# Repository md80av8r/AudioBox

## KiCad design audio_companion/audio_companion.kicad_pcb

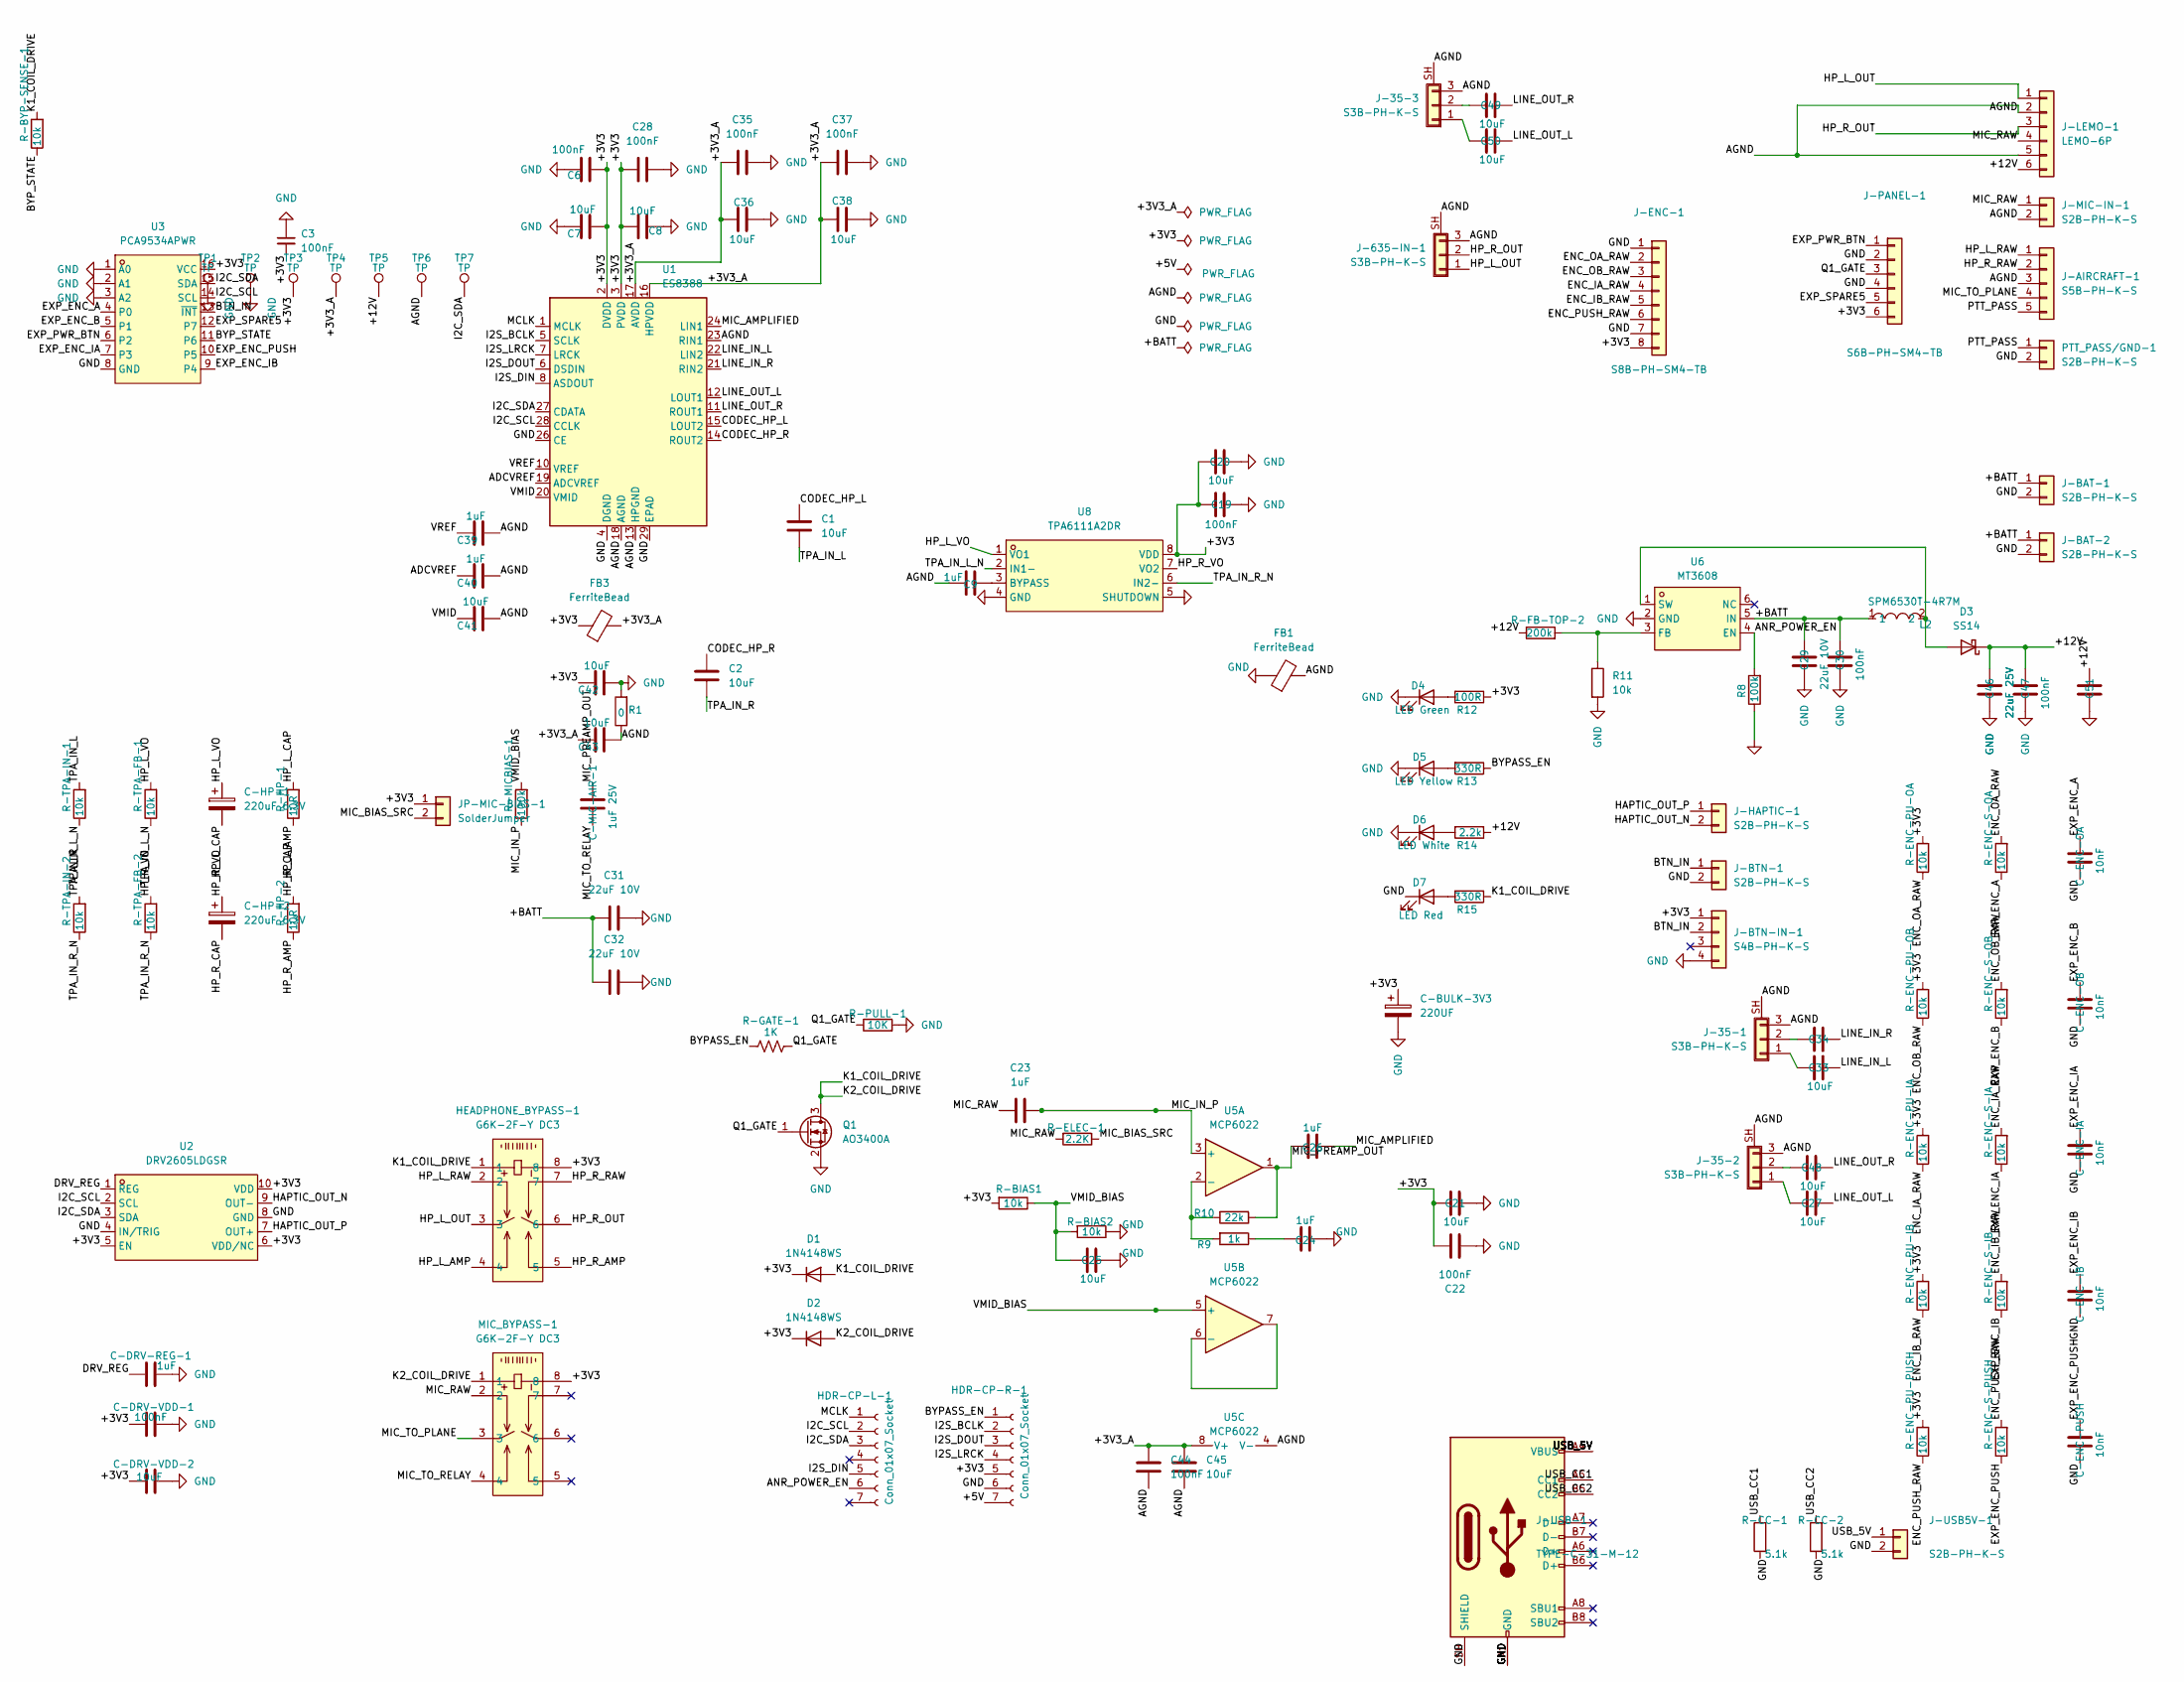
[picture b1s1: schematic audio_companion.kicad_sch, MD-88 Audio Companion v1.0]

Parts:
C1, C2: 10uF; C_0805_2012Metric
C3, C6, C19, C22, C28, C30, C35, C37, C44, C47: 100nF; C_0402_1005Metric
C7, C8, C20, C21, C25, C27, C33, C34, C36, C38, C41, C42, C43, C45, C48, C49, C50: 10uF; C_0402_1005Metric
C9, C23, C24, C26, C39, C40: 1uF; C_0402_1005Metric
C29, C31, C32: 22uF 10V; C_0805_2012Metric
C46, C51: 22uF 25V; C_0805_2012Metric
C-BULK-3V3: 220UF; CP_EIA-6032-28_Kemet-C
C-DRV-REG-1: 1uF; C_0402_1005Metric
C-DRV-VDD-1: 100nF; C_0402_1005Metric
C-DRV-VDD-2: 10uF; C_0402_1005Metric
C-ENC-IA: 10nF; C_0402_1005Metric
C-ENC-IB: 10nF; C_0402_1005Metric
C-ENC-OA: 10nF; C_0402_1005Metric
C-ENC-OB: 10nF; C_0402_1005Metric
C-ENC-PUSH: 10nF; C_0402_1005Metric
C-HP-1, C-HP-2: 220uF 6.3V; CP_EIA-6032-28_Kemet-C
C-MIC-AIR-1: 1uF 25V; C_0402_1005Metric
D1, D2: 1N4148WS; D_SOD-323
D3: SS14; D_SMA
D4: LED Green; LED_0603_1608Metric
D5: LED Yellow; LED_0603_1608Metric
D6: LED White; LED_0603_1608Metric
D7: LED Red; LED_0603_1608Metric
FB1, FB3: FerriteBead; L_0603_1608Metric
HDR-CP-L-1: Conn_01x07_Socket; PinHeader_1x07_P2.54mm_Vertical
HDR-CP-R-1: Conn_01x07_Socket; PinHeader_1x07_P2.54mm_Vertical
HEADPHONE_BYPASS-1: G6K-2F-Y DC3; Relay_DPDT_Omron_G6K-2F-Y; MPN G6K-2F-Y DC3; LCSC Part C93168
J-35-1, J-35-2, J-35-3, J-635-IN-1: S3B-PH-K-S; JST_PH_S3B-PH-K_1x03_P2.00mm_Horizontal
J-AIRCRAFT-1: S5B-PH-K-S; JST_PH_S5B-PH-K_1x05_P2.00mm_Horizontal
J-BAT-1, J-BAT-2: S2B-PH-K-S; JST_PH_S2B-PH-K_1x02_P2.00mm_Horizontal
J-BTN-1: S2B-PH-K-S; JST_PH_S2B-PH-K_1x02_P2.00mm_Horizontal
J-BTN-IN-1: S4B-PH-K-S; JST_PH_S4B-PH-K_1x04_P2.00mm_Horizontal
J-ENC-1: S8B-PH-SM4-TB; JST_PH_S8B-PH-SM4-TB_1x08-1MP_P2.00mm_Horizontal; MPN S8B-PH-SM4-TB(LF)(SN)
J-HAPTIC-1: S2B-PH-K-S; JST_PH_S2B-PH-K_1x02_P2.00mm_Horizontal
J-LEMO-1: LEMO-6P; PinHeader_1x06_P2.54mm_Vertical
J-MIC-IN-1: S2B-PH-K-S; JST_PH_S2B-PH-K_1x02_P2.00mm_Horizontal
J-PANEL-1: S6B-PH-SM4-TB; JST_PH_S6B-PH-SM4-TB_1x06-1MP_P2.00mm_Horizontal; MPN S6B-PH-SM4-TB(LF)(SN)
J-USB5V-1: S2B-PH-K-S; JST_PH_S2B-PH-K_1x02_P2.00mm_Horizontal; MPN S2B-PH-K-S
J-USB-1: TYPE-C-31-M-12; USB_C_Receptacle_HRO_TYPE-C-31-M-12; MPN TYPE-C-31-M-12; LCSC C165948
JP-MIC-BIAS-1: SolderJumper; SolderJumper-2_P1.3mm_Open_Pad1.0x1.5mm
L2: SPM6530T-4R7M; IND-SMD_L7.1-W6.5; MPN SPM6530T-4R7M; LCSC Part C76857
MIC_BYPASS-1: G6K-2F-Y DC3; Relay_DPDT_Omron_G6K-2F-Y; MPN G6K-2F-Y DC3; LCSC Part C93168
PTT_PASS/GND-1: S2B-PH-K-S; JST_PH_S2B-PH-K_1x02_P2.00mm_Horizontal
Q1: AO3400A; SOT-23
R1: 0; R_0402_1005Metric
R8: 100k; R_0402_1005Metric
R9: 1k; R_0402_1005Metric
R10: 22k; R_0402_1005Metric
R11: 10k; R_0402_1005Metric
R12: 100R; R_0402_1005Metric
R13, R15: 330R; R_0402_1005Metric
R14: 2.2k; R_0402_1005Metric
R-BIAS1, R-BIAS2: 10k; R_0402_1005Metric
R-BYP-SENSE-1: 10k; R_0402_1005Metric
R-CC-1, R-CC-2: 5.1k; R_0402_1005Metric; LCSC C25905
R-ELEC-1: 2.2K; R_0402_1005Metric
R-ENC-PU-IA: 10k; R_0402_1005Metric
R-ENC-PU-IB: 10k; R_0402_1005Metric
R-ENC-PU-OA: 10k; R_0402_1005Metric
R-ENC-PU-OB: 10k; R_0402_1005Metric
R-ENC-PU-PUSH: 10k; R_0402_1005Metric
R-ENC-S-IA: 10k; R_0402_1005Metric
R-ENC-S-IB: 10k; R_0402_1005Metric
R-ENC-S-OA: 10k; R_0402_1005Metric
R-ENC-S-OB: 10k; R_0402_1005Metric
R-ENC-S-PUSH: 10k; R_0402_1005Metric
R-FB-TOP-2: 200k; R_0402_1005Metric
R-GATE-1: 1K; R_0402_1005Metric
R-HP-1, R-HP-2: 10R; R_0402_1005Metric
R-MICBIAS-1: 100k; R_0402_1005Metric
R-PULL-1: 10K; R_0402_1005Metric
R-TPA-FB-1, R-TPA-FB-2: 10k; R_0402_1005Metric
R-TPA-IN-1, R-TPA-IN-2: 10k; R_0402_1005Metric
TP1, TP2, TP3, TP4, TP5, TP6, TP7: TP; TestPoint_Pad_D1.5mm
U1: ES8388; QFN-28-1EP_4x4mm_P0.45mm_EP2.6x2.6mm
U2: DRV2605LDGSR; VSSOP-10_L3.0-W3.0-P0.50-LS4.9-BL; MPN DRV2605LDGSR; LCSC Part C527464
U3: PCA9534APWR; TSSOP-16_L5.0-W4.4-P0.65-LS6.4-BL; MPN PCA9534APWR; LCSC Part C2871127
U5: MCP6022; SOIC-8_3.9x4.9mm_P1.27mm
U6: MT3608; SOT-23-6_L2.9-W1.6-P0.95-LS2.8-BL; MPN MT3608; LCSC Part C84817
U8: TPA6111A2DR; SOIC-8_L5.0-W4.0-P1.27-LS6.0-BL; MPN TPA6111A2DR; LCSC Part C497472

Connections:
/+3V3: C3.2, C6.1, C7.1, C8.1, C19.2, C20.1, C21.1, C22.2, C28.1, C42.2, C-BULK-3V3.1, C-DRV-VDD-1.1, C-DRV-VDD-2.1, D1.1 (K), D2.1 (K), FB3.1, HDR-CP-R-1.5, HEADPHONE_BYPASS-1.8, J-BTN-IN-1.1, J-ENC-1.8, J-PANEL-1.6, JP-MIC-BIAS-1.1, MIC_BYPASS-1.8, R12.1, R-BIAS1.2, R-ENC-PU-IA.2, R-ENC-PU-IB.2, R-ENC-PU-OA.2, R-ENC-PU-OB.2, R-ENC-PU-PUSH.2, TP3.1, U1.2 (DVDD), U1.3 (PVDD), U2.5 (EN), U2.6 (VDD/NC), U2.10 (VDD), U3.16 (VCC), U8.8 (VDD)
/+3V3_A: C35.1, C36.1, C37.1, C38.1, C43.2, C44.1, C45.1, FB3.2, TP4.1, U1.16 (HPVDD), U1.17 (AVDD), U5.8 (V+)
/+5V: HDR-CP-R-1.7
/+12V: C46.1, C47.1, C51.1, D3.1 (K), J-LEMO-1.6, R14.1, R-FB-TOP-2.1, TP5.1
/+BATT: C29.1, C30.1, C31.2, C32.2, J-BAT-1.1, J-BAT-2.1, L2.1, U6.5 (IN)
/ADCVREF: C40.2, U1.19 (ADCVREF)
/AGND: C9.1, C39.1, C40.1, C41.1, C43.1, C44.2, C45.2, FB1.2, J-35-1.3, J-35-1.SH (Shield), J-35-2.3, J-35-2.SH (Shield), J-35-3.3, J-35-3.SH (Shield), J-635-IN-1.3, J-635-IN-1.SH (Shield), J-AIRCRAFT-1.3, J-LEMO-1.2, J-LEMO-1.5, J-MIC-IN-1.2, R1.1, TP6.1, U1.13 (HPGND), U1.18 (AGND), U1.23 (RIN1), U5.4 (V-)
/ANR_POWER_EN: HDR-CP-L-1.6, R8.2, U6.4 (EN)
/BTN_IN: J-BTN-1.1, J-BTN-IN-1.2, U3.13 (~INT)
/BYPASS_EN: HDR-CP-R-1.1, R13.1, R-GATE-1.1
/BYP_STATE: R-BYP-SENSE-1.1, U3.11 (P6)
/CODEC_HP_L: C1.2, U1.15 (LOUT2)
/CODEC_HP_R: C2.2, U1.14 (ROUT2)
/DRV_REG: C-DRV-REG-1.1, U2.1 (REG)
/ENC_IA_RAW: J-ENC-1.4, R-ENC-PU-IA.1, R-ENC-S-IA.2
/ENC_IB_RAW: J-ENC-1.5, R-ENC-PU-IB.1, R-ENC-S-IB.2
/ENC_OA_RAW: J-ENC-1.2, R-ENC-PU-OA.1, R-ENC-S-OA.2
/ENC_OB_RAW: J-ENC-1.3, R-ENC-PU-OB.1, R-ENC-S-OB.2
/ENC_PUSH_RAW: J-ENC-1.6, R-ENC-PU-PUSH.1, R-ENC-S-PUSH.2
/EXP_ENC_A: C-ENC-OA.1, R-ENC-S-OA.1, U3.4 (P0)
/EXP_ENC_B: C-ENC-OB.1, R-ENC-S-OB.1, U3.5 (P1)
/EXP_ENC_IA: C-ENC-IA.1, R-ENC-S-IA.1, U3.7 (P3)
/EXP_ENC_IB: C-ENC-IB.1, R-ENC-S-IB.1, U3.9 (P4)
/EXP_ENC_PUSH: C-ENC-PUSH.1, R-ENC-S-PUSH.1, U3.10 (P5)
/EXP_PWR_BTN: J-PANEL-1.1, U3.6 (P2)
/EXP_SPARE5: J-PANEL-1.5, U3.12 (P7)
/HAPTIC_OUT_N: J-HAPTIC-1.2, U2.9 (OUT-)
/HAPTIC_OUT_P: J-HAPTIC-1.1, U2.7 (OUT+)
/HP_L_AMP: HEADPHONE_BYPASS-1.4, R-HP-1.1
/HP_L_CAP: C-HP-1.2, R-HP-1.2
/HP_L_OUT: HEADPHONE_BYPASS-1.3, J-635-IN-1.1, J-LEMO-1.1
/HP_L_RAW: HEADPHONE_BYPASS-1.2, J-AIRCRAFT-1.1
/HP_L_VO: C-HP-1.1, R-TPA-FB-1.2, U8.1 (VO1)
/HP_R_AMP: HEADPHONE_BYPASS-1.5, R-HP-2.1
/HP_R_CAP: C-HP-2.2, R-HP-2.2
/HP_R_OUT: HEADPHONE_BYPASS-1.6, J-635-IN-1.2, J-LEMO-1.3
/HP_R_RAW: HEADPHONE_BYPASS-1.7, J-AIRCRAFT-1.2
/HP_R_VO: C-HP-2.1, R-TPA-FB-2.2, U8.7 (VO2)
/I2C_SCL: HDR-CP-L-1.2, U1.28 (CCLK), U2.2 (SCL), U3.14 (SCL)
/I2C_SDA: HDR-CP-L-1.3, TP7.1, U1.27 (CDATA), U2.3 (SDA), U3.15 (SDA)
/I2S_BCLK: HDR-CP-R-1.2, U1.5 (SCLK)
/I2S_DIN: HDR-CP-L-1.5, U1.8 (ASDOUT)
/I2S_DOUT: HDR-CP-R-1.3, U1.6 (DSDIN)
/I2S_LRCK: HDR-CP-R-1.4, U1.7 (LRCK)
/K1_COIL_DRIVE: D1.2 (A), D2.2 (A), HEADPHONE_BYPASS-1.1, MIC_BYPASS-1.1, Q1.3 (D), R15.1, R-BYP-SENSE-1.2
/LINE_IN_L: C33.2, U1.22 (LIN2)
/LINE_IN_R: C34.2, U1.21 (RIN2)
/LINE_OUT_L: C27.2, C50.2, U1.12 (LOUT1)
/LINE_OUT_R: C48.2, C49.2, U1.11 (ROUT1)
/MCLK: HDR-CP-L-1.1, U1.1 (MCLK)
/MIC_AMPLIFIED: C26.1, U1.24 (LIN1)
/MIC_BIAS_SRC: JP-MIC-BIAS-1.2, R-ELEC-1.1
/MIC_IN_P: C23.1, R-MICBIAS-1.1, U5.3 (+)
/MIC_PREAMP_OUT: C26.2, C-MIC-AIR-1.1, R10.1, U5.1
/MIC_RAW: C23.2, J-LEMO-1.4, J-MIC-IN-1.1, MIC_BYPASS-1.2, R-ELEC-1.2
/MIC_TO_PLANE: J-AIRCRAFT-1.4, MIC_BYPASS-1.3
/MIC_TO_RELAY: C-MIC-AIR-1.2, MIC_BYPASS-1.4
/PTT_PASS: J-AIRCRAFT-1.5, PTT_PASS/GND-1.1
/Q1_GATE: J-PANEL-1.3, Q1.1 (G), R-GATE-1.2, R-PULL-1.1
/TPA_IN_L: C1.1, R-TPA-IN-1.2
/TPA_IN_L_N: R-TPA-FB-1.1, R-TPA-IN-1.1, U8.2 (IN1-)
/TPA_IN_R: C2.1, R-TPA-IN-2.2
/TPA_IN_R_N: R-TPA-FB-2.1, R-TPA-IN-2.1, U8.6 (IN2-)
/USB_5V: J-USB5V-1.1, J-USB-1.A4 (VBUS), J-USB-1.A9 (VBUS), J-USB-1.B4 (VBUS), J-USB-1.B9 (VBUS)
/USB_CC1: J-USB-1.A5 (CC1), R-CC-1.2
/USB_CC2: J-USB-1.B5 (CC2), R-CC-2.2
/VMID: C41.2, U1.20 (VMID)
/VMID_BIAS: C25.1, R-BIAS1.1, R-BIAS2.2, R-MICBIAS-1.2, U5.5 (+)
/VREF: C39.2, U1.10 (VREF)
GND: C3.1, C6.2, C7.2, C8.2, C19.1, C20.2, C21.2, C22.1, C24.1, C25.2, C28.2, C29.2, C30.2, C31.1, C32.1, C35.2, C36.2, C37.2, C38.2, C42.1, C46.2, C47.2, C51.2, C-BULK-3V3.2, C-DRV-REG-1.2, C-DRV-VDD-1.2, C-DRV-VDD-2.2, C-ENC-IA.2, C-ENC-IB.2, C-ENC-OA.2, C-ENC-OB.2, C-ENC-PUSH.2, D4.1 (K), D5.1 (K), D6.1 (K), D7.1 (K), FB1.1, HDR-CP-R-1.6, J-BAT-1.2, J-BAT-2.2, J-BTN-1.2, J-BTN-IN-1.4, J-ENC-1.1, J-ENC-1.7, J-PANEL-1.2, J-PANEL-1.4, J-USB5V-1.2, J-USB-1.A1 (GND), J-USB-1.A12 (GND), J-USB-1.B1 (GND), J-USB-1.B12 (GND), J-USB-1.SH (SHIELD), PTT_PASS/GND-1.2, Q1.2 (S), R1.2, R8.1, R11.2, R-BIAS2.1, R-CC-1.1, R-CC-2.1, R-PULL-1.2, TP1.1, TP2.1, U1.4 (DGND), U1.26 (CE), U1.29 (EPAD), U2.4 (IN/TRIG), U2.8 (GND), U3.1 (A0), U3.2 (A1), U3.3 (A2), U3.8 (GND), U6.2 (GND), U8.4 (GND), U8.5 (SHUTDOWN); also elsewhere on the board
unnamed: C24.2, R9.1
unnamed: D3.2 (A), L2.2, U6.1 (SW)
unnamed: D4.2 (A), R12.2
unnamed: D5.2 (A), R13.2
unnamed: D6.2 (A), R14.2
unnamed: D7.2 (A), R15.2
unnamed: C33.1, J-35-1.1
unnamed: C34.1, J-35-1.2
unnamed: C27.1, J-35-2.1
unnamed: C48.1, J-35-2.2
unnamed: C50.1, J-35-3.1
unnamed: C49.1, J-35-3.2
unnamed: R9.2, R10.2, U5.2 (-)
unnamed: U5.6 (-), U5.7
unnamed: R11.1, R-FB-TOP-2.2, U6.3 (FB)
unnamed: C9.2, U8.3 (BYPASS)

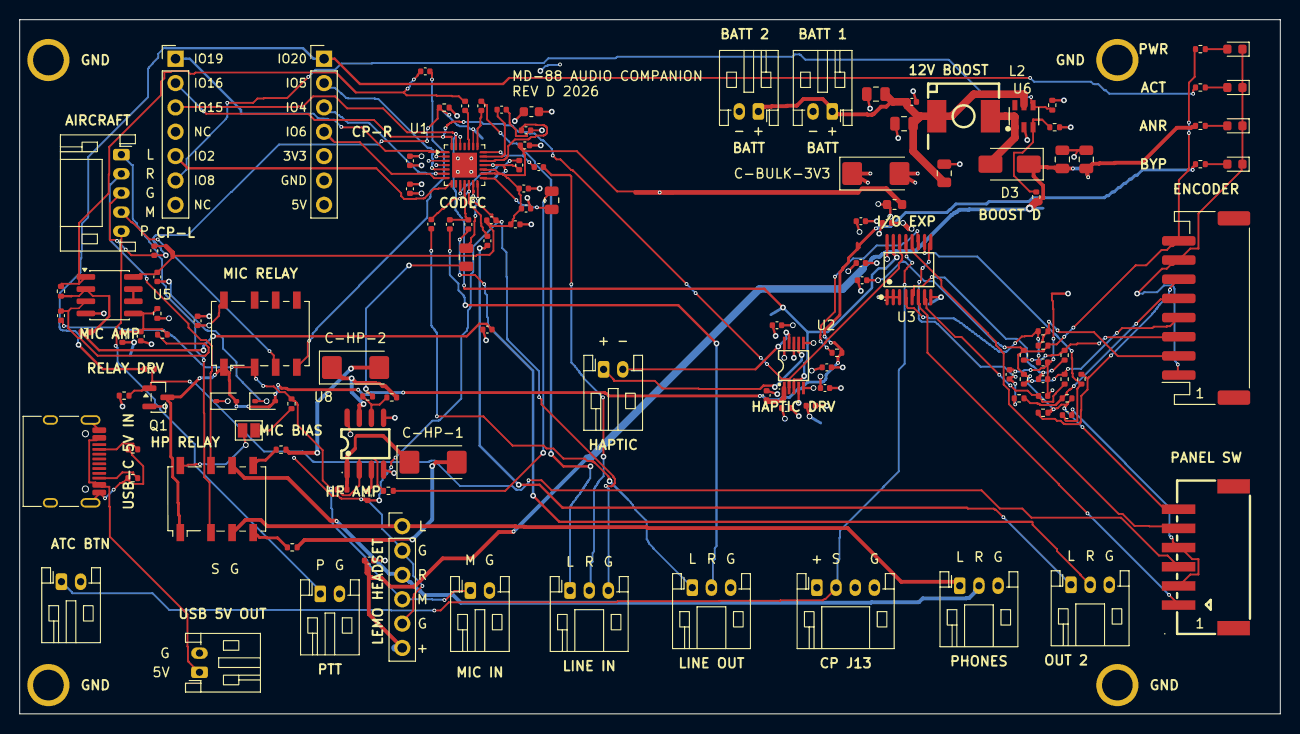
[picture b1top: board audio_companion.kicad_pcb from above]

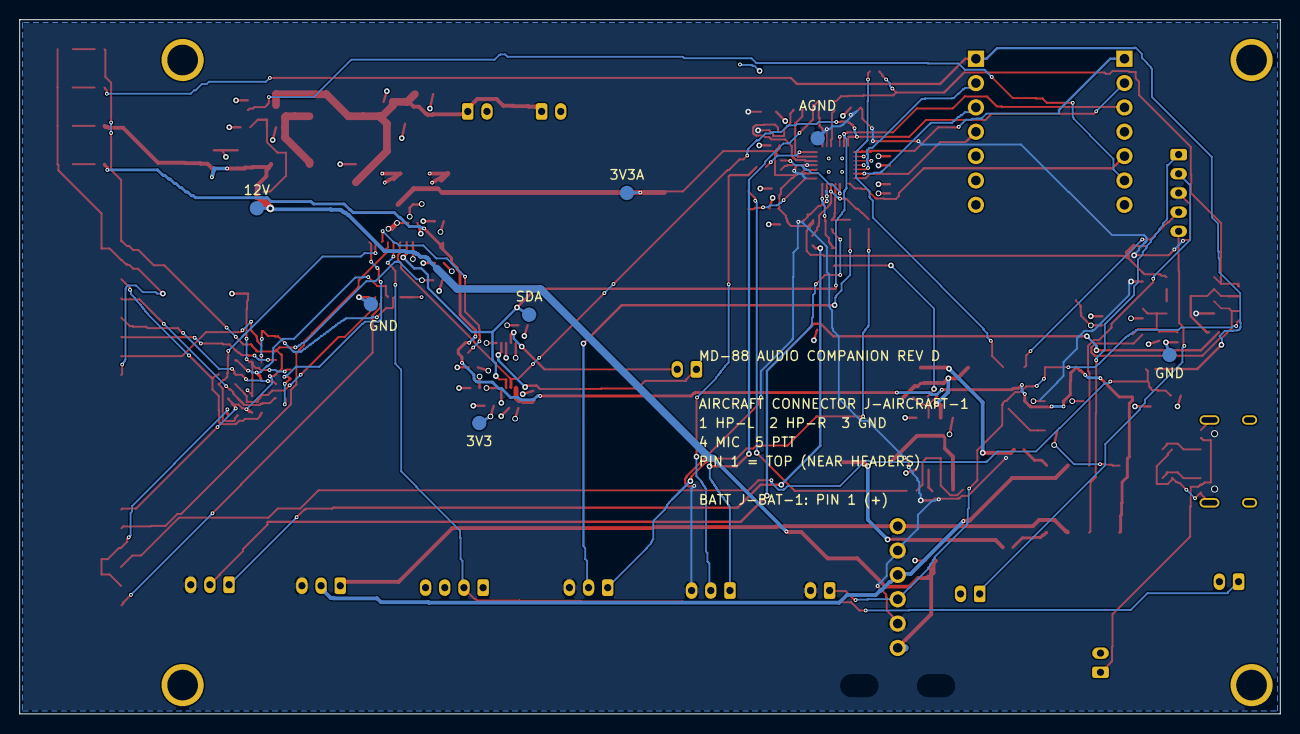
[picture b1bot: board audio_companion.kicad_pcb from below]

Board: 4 copper layers, 131.5 x 72.4 mm, 137 parts (7 on the bottom side), 85 nets.

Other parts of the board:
H1, H2, H3, H4: MountingHole_3.2mm_M3_NPTH; MountingHole_3.2mm_M3

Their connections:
GND: H1.1, H2.1, H3.1, H4.1; also elsewhere on the board

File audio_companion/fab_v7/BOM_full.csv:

Value,Designators,Qty,Package,Manufacturer part,LCSC #,Assembly,Notes
S5B-PH-K-S,J-AIRCRAFT-1,1,THT,S5B-PH-K-S(LF)(SN),C157923,hand solder,JST PH 5-pin side entry
S4B-PH-K-S,J-BTN-IN-1,1,THT,S4B-PH-K-S(LF)(SN),C157926,hand solder,JST PH 4-pin side entry
S3B-PH-K-S,"J-35-1,J-35-2,J-35-3,J-635-IN-1",4,THT,S3B-PH-K-S(LF)(SN),C157929,hand solder,JST PH 3-pin side entry
S2B-PH-K-S,"J-BAT-1,J-BAT-2,J-BTN-1,J-HAPTIC-1,J-MIC-IN-1,J-USB5V-1,PTT_PASS/GND-1",7,THT,S2B-PH-K-S(LF)(SN),C173752,hand solder,JST PH 2-pin side entry
Conn_01x07_Socket,"HDR-CP-L-1,HDR-CP-R-1",2,THT,"1x7 male header, 19mm LONG pins",NOT_ON_LCSC,hand solder,"stack-on to CrowPanel - source separately, pin length must bridge the 10mm gap"
LEMO-6P,J-LEMO-1,1,holes,(6 plated holes),-,no part,LEMO pigtail wires soldered direct + zip-tie slots
SolderJumper,JP-MIC-BIAS-1,1,pads,(PCB pads only),-,no part,MIC BIAS jumper - bridge with solder to enable electret bias
TP,"TP1,TP2,TP3,TP4,TP5,TP6,TP7",7,pads,(PCB pads only),-,no part,bottom test pads
1k,"R9,R-GATE-1",2,0402,0402WGF1001TCE,C11702,JLCPCB assembles,1k
LED Green,D4,1,0603,KT-0603G,C12624,JLCPCB assembles,PWR - emerald green
10nF,"C-ENC-IA,C-ENC-IB,C-ENC-OA,C-ENC-OB,C-ENC-PUSH",5,0402,CL05B103KB5NNNC,C15195,JLCPCB assembles,10nF 50V X7R - encoder debounce
100nF,"C3,C6,C19,C22,C28,C30,C35,C37,C44,C47,C-DRV-VDD-1",11,0402,CL05B104KO5NNNC,C1525,JLCPCB assembles,100nF 16V X7R
10uF,"C7,C8,C20,C21,C25,C27,C33,C34,C36,C38,C41,C42,C43,C45,C48,C49,C50,C-DRV-VDD-2",18,0402,CL05A106MQ5NUNC,C15525,JLCPCB assembles,10uF 6.3V X5R (3V3 rails only)
10uF,"C1,C2",2,0805,CL21A106KAYNNNE,C15850,JLCPCB assembles,10uF 25V X5R
TYPE-C-31-M-12,J-USB-1,1,USB-C 16P SMD,TYPE-C-31-M-12,C165948,JLCPCB assembles,power-in jack (left edge)
0,R1,1,0402,0402WGF0000TCE,C17168,JLCPCB assembles,0R AGND/GND tie
FerriteBead,"FB1,FB3",2,0603,BLM18AG601SN1D,C19330,JLCPCB assembles,600R@100MHz 500mA
220UF,C-BULK-3V3,1,6032-28,T491C227M006AT,C1952817,JLCPCB assembles,220uF 6.3V tantalum - + toward pad 1 marking
220uF 6.3V,"C-HP-1,C-HP-2",2,6032-28,T491C227M006AT,C1952817,JLCPCB assembles,"220uF 6.3V tantalum - headphone output coupling, + toward TPA"
AO3400A,Q1,1,SOT-23,AO3400A,C20917,JLCPCB assembles,"relay driver, logic-level 30V 5.7A, Basic"
1N4148WS,"D1,D2",2,SOD-323,1N4148WS,C2128,JLCPCB assembles,relay flyback
G6K-2F-Y DC3,"HEADPHONE_BYPASS-1,MIC_BYPASS-1",2,SMD 10x6.5,G6K-2F-Y-TR DC3,C2153097,JLCPCB assembles,"Omron DPDT 3V coil SMT (alt C93168, not recommended for new designs)"
LED Red,D7,1,0603,KT-0603R,C2286,JLCPCB assembles,BYPASS - red
LED Yellow,D5,1,0603,KT-0603Y,C2287,JLCPCB assembles,ACTIVE - yellow
LED White,D6,1,0603,KT-0603W,C2290,JLCPCB assembles,ANR 12V - white
SS14,D3,1,SMA,SS14,C2480,JLCPCB assembles,Schottky 40V 1A - boost rectifier
100R,R12,1,0402,0402WGF1000TCE,C25076,JLCPCB assembles,100R
10R,"R-HP-1,R-HP-2",2,0402,0402WGF100JTCE,C25077,JLCPCB assembles,10R
330R,"R13,R15",2,0402,0402WGF3300TCE,C25104,JLCPCB assembles,330R
100k,"R8,R-MICBIAS-1",2,0402,0402WGF1003TCE,C25741,JLCPCB assembles,100k
10k,"R11,R-BIAS1,R-BIAS2,R-BYP-SENSE-1,R-ENC-PU-IA,R-ENC-PU-IB,R-ENC-PU-OA,R-ENC-PU-OB,R-ENC-PU-PUSH,R-ENC-S-IA,R-ENC-S-IB,R-ENC-S-OA,R-ENC-S-OB,R-ENC-S-PUSH,R-PULL-1,R-TPA-FB-1,R-TPA-FB-2,R-TPA-IN-1,R-TPA-IN-2",19,0402,0402WGF1002TCE,C25744,JLCPCB assembles,10k
200k,R-FB-TOP-2,1,0402,0402WGF2003TCE,C25764,JLCPCB assembles,200k
22k,R10,1,0402,0402WGF2202TCE,C25768,JLCPCB assembles,22k
2.2k,"R14,R-ELEC-1",2,0402,0402WGF2201TCE,C25879,JLCPCB assembles,2.2k
5.1k,"R-CC-1,R-CC-2",2,0402,0402WGF5101TCE,C25905,JLCPCB assembles,5.1k CC pull-down for USB-C power-in
S8B-PH-SM4-TB,J-ENC-1,1,JST PH 8P SMD side,S8B-PH-SM4-TB(LF)(SN),C265121,JLCPCB assembles,encoder cable connector
S6B-PH-SM4-TB,J-PANEL-1,1,JST PH 6P SMD side,S6B-PH-SM4-TB(LF)(SN),C265405,JLCPCB assembles,panel switches cable connector
PCA9534APWR,U3,1,TSSOP-16,PCA9534APWR,C2871127,JLCPCB assembles,I2C IO expander
ES8388,U1,1,QFN-28-EP(4x4),ES8388,C365736,JLCPCB assembles,audio codec
22uF 10V,"C29,C31,C32",3,0805,CL21A226MAQNNNE,C45783,JLCPCB assembles,22uF 25V X5R (covers 10V use)
22uF 25V,"C46,C51",2,0805,CL21A226MAQNNNE,C45783,JLCPCB assembles,"22uF 25V X5R - boost output, must be >=25V"
TPA6111A2DR,U8,1,SOIC-8,TPA6111A2DR,C497472,JLCPCB assembles,headphone amp
DRV2605LDGSR,U2,1,VSSOP-10,DRV2605LDGSR,C527464,JLCPCB assembles,haptic driver
1uF,"C9,C23,C24,C26,C39,C40,C-DRV-REG-1",7,0402,CL05A105KA5NQNC,C52923,JLCPCB assembles,1uF 25V X5R
1uF 25V,C-MIC-AIR-1,1,0402,CL05A105KA5NQNC,C52923,JLCPCB assembles,"1uF 25V X5R - mic DC block, keep >=16V"
MCP6022,U5,1,SOIC-8,MCP6022T-I/SN,C57639,JLCPCB assembles,dual op amp
SPM6530T-4R7M,L2,1,7.1x6.5,SPM6530T-4R7M,C76857,JLCPCB assembles,TDK 4.7uH 5.6A
MT3608,U6,1,SOT-23-6,MT3608,C84817,JLCPCB assembles,12V boost

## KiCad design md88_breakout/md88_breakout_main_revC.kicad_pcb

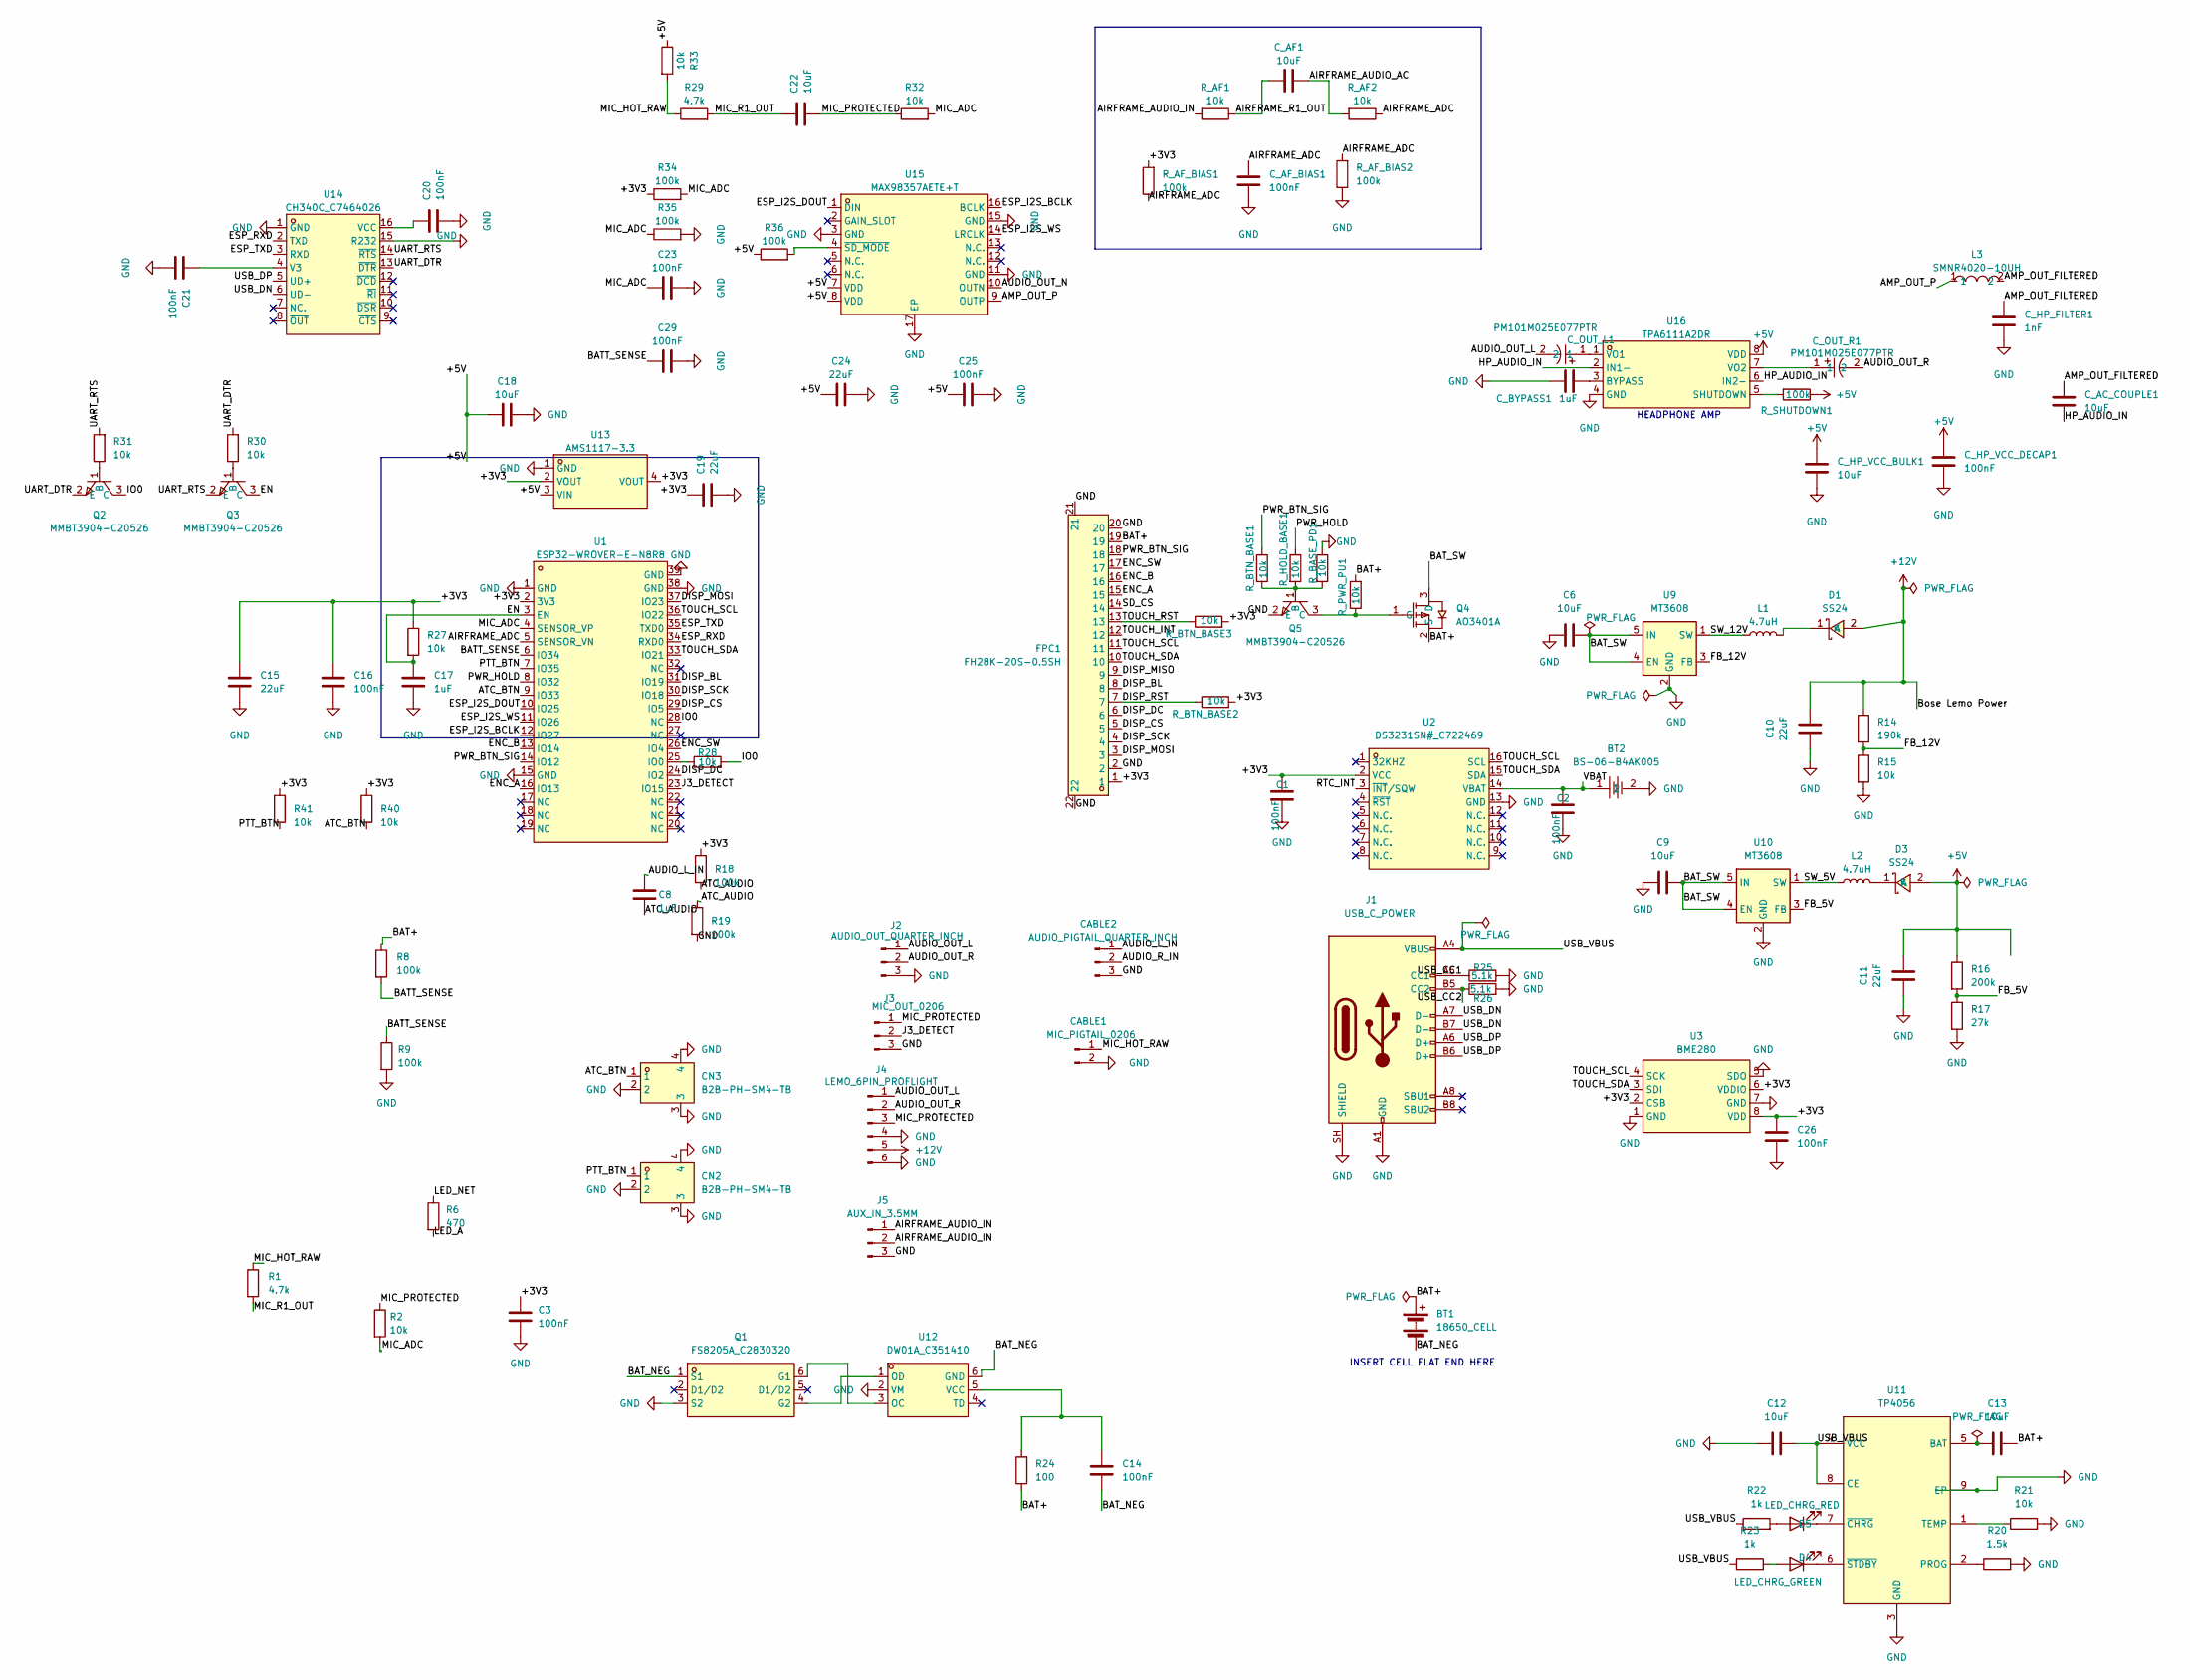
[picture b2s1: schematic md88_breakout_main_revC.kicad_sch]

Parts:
BT1: 18650_CELL; CONN-SMD_B2B-PH-SM4-TB-LF-SN
BT2: BS-06-B4AK005; BAT-SMD_BS-CR2032-8; MPN BS-06-B4AK005; LCSC Part C964766
C1, C2, C3, C14, C16, C20, C21, C23, C25, C26, C29: 100nF; C_0805_2012Metric
C6, C9, C12, C13, C18: 10uF; C_0805_2012Metric
C8, C17: 1uF; C_0805_2012Metric
C10, C11, C15, C19, C24: 22uF; C_0805_2012Metric
C22: 10uF; C_1210_3225Metric
CABLE1: MIC_PIGTAIL_0206; CONN-SMD_B2B-PH-SM4-TB-LF-SN
CABLE2: AUDIO_PIGTAIL_QUARTER_INCH; CONN-SMD_B3B-PH-SM4-TB-LF-SN
CN2, CN3: B2B-PH-SM4-TB; CONN-SMD_B2B-PH-SM4-TB-LF-SN; MPN B2B-PH-SM4-TB(LF)(SN); LCSC Part C160352
C_AC_COUPLE1: 10uF; C_1210_3225Metric
C_AF1: 10uF; C_1210_3225Metric
C_AF_BIAS1: 100nF; C_1210_3225Metric
C_BYPASS1: 1uF; C_0805_2012Metric
C_HP_FILTER1: 1nF; C_0805_2012Metric
C_HP_VCC_BULK1: 10uF; C_0805_2012Metric
C_HP_VCC_DECAP1: 100nF; C_0805_2012Metric
C_OUT_L1: PM101M025E077PTR; CAP-SMD_BD6.3-L6.6-W6.6-LS7.2-FD; MPN PM101M025E077PTR; LCSC Part C2858382
C_OUT_R1: PM101M025E077PTR; CAP-SMD_BD6.3-L6.6-W6.6-LS7.2-FD; MPN PM101M025E077PTR; LCSC Part C2858382
D1, D3: SS24; SMA_L4.3-W2.6-LS5.2-RD; MPN SS24; LCSC Part C50645
D4: LED_CHRG_RED; LED_0805_2012Metric
D5: LED_CHRG_GREEN; LED_0805_2012Metric
FPC1: FH28K-20S-0.5SH; CONN-SMD_FH28K-20S-0.5SH; MPN FH28K-20S-0.5SH; LCSC Part C3168665
J1: USB_C_POWER; USB_C_Receptacle_HRO_TYPE-C-31-M-12
J2: AUDIO_OUT_QUARTER_INCH; CONN-SMD_B3B-PH-SM4-TB-LF-SN
J3: MIC_OUT_0206; CONN-SMD_B3B-PH-SM4-TB-LF-SN
J4: LEMO_6PIN_PROFLIGHT; CONN-SMD_6P-P2.00_B6B-PH-SM4-TB-LF-SN
J5: AUX_IN_3.5MM; CONN-SMD_B3B-PH-SM4-TB-LF-SN
L1, L2: 4.7uH; IND-SMD_L4.0-W4.0_LQH44PN2R2MP0L
L3: SMNR4020-10UH; IND-SMD_L4.0-W4.0_LQH44PN2R2MP0L; MPN SMNR4020-10UH; LCSC Part C135263
Q1: FS8205A_C2830320; SOT-23-6_L2.9-W1.6-P0.95-LS2.8-BR; MPN FS8205A; LCSC Part C2830320
Q2, Q3, Q5: MMBT3904-C20526; SOT-23-3_L2.9-W1.3-P1.90-LS2.4-BR; MPN MMBT3904(RANGE:100-300); LCSC Part C20526
Q4: AO3401A; SOT-23_L2.9-W1.3-P1.90-LS2.4-BR; MPN AO3401A; LCSC Part C15127
R1, R29: 4.7k; R_0805_2012Metric
R2, R15, R21, R27, R28, R30, R31, R32, R33, R40, R41: 10k; R_0805_2012Metric
R6: 470; R_0805_2012Metric
R8, R9, R18, R19, R34, R35, R36: 100k; R_0805_2012Metric
R14: 190k; R_0805_2012Metric
R16: 200k; R_0805_2012Metric
R17: 27k; R_0805_2012Metric
R20: 1.5k
R22, R23: 1k; R_0805_2012Metric
R24: 100; R_0805_2012Metric
R25, R26: 5.1k; R_0805_2012Metric
R_AF1, R_AF2: 10k; R_0805_2012Metric
R_AF_BIAS1, R_AF_BIAS2: 100k; R_0805_2012Metric
R_BASE_PD1: 10k; R_0805_2012Metric
R_BTN_BASE1, R_BTN_BASE2, R_BTN_BASE3: 10k; R_0805_2012Metric
R_HOLD_BASE1: 10k; R_0805_2012Metric
R_PWR_PU1: 10k; R_0805_2012Metric
R_SHUTDOWN1: 100k; R_0805_2012Metric
U1: ESP32-WROVER-E-N8R8; WIFI-SMD_ESP32-WROVER-IE8MB; MPN ESP32-WROVER-E-N8R8; LCSC Part C2973667
U2: DS3231SN#_C722469; SOIC-16_L10.3-W7.5-P1.27-LS10.3-BL; MPN DS3231SN#; LCSC Part C722469
U3: BME280; LGA-8_BME280_BL; MPN BME280; LCSC Part C92489
U9, U10: MT3608; SOT-23-6
U11: TP4056; ESOP-8_L4.9-W3.9-P1.27-LS6.0-BL-EP; MPN TP4056-42-ESOP8; LCSC Part C16581
U12: DW01A_C351410; SOT-23-6_L2.9-W1.6-P0.95-LS2.8-BL; MPN DW01A; LCSC Part C351410
U13: AMS1117-3.3; SOT-223-3_L6.5-W3.4-P2.30-LS7.0-BR; MPN AMS1117-3.3; LCSC Part C6186
U14: CH340C_C7464026; SOP-16_L10.0-W3.9-P1.27-LS6.0-BL; MPN CH340C; LCSC Part C7464026
U15: MAX98357AETE+T; TQFN-16_L3.0-W3.0-P0.50-BL-EP1.5; MPN MAX98357AETE+T; LCSC Part C910544
U16: TPA6111A2DR; SOIC-8_L5.0-W4.0-P1.27-LS6.0-BL; MPN TPA6111A2DR; LCSC Part C497472

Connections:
+5V: C11.2, C18.2, C24.1, C25.1, C_HP_VCC_BULK1.1, C_HP_VCC_DECAP1.1, D3.2 (A), R16.1, R33.1, R36.1, R_SHUTDOWN1.1, U13.3 (VIN), U15.7 (VDD), U15.8 (VDD), U16.8 (VDD)
+12V: C10.2, D1.2 (A), J4.5, R14.1
/+3V3: C1.2, C3.1, C15.1, C16.1, C19.2, C26.1, FPC1.1, R18.1, R27.1, R34.1, R40.1, R41.1, R_AF_BIAS1.2, R_BTN_BASE2.2, R_BTN_BASE3.2, U1.2 (3V3), U2.2 (VCC), U3.2 (CSB), U3.6 (VDDIO), U3.8 (VDD), U13.2 (VOUT), U13.4 (VOUT)
/AIRFRAME_ADC: C_AF_BIAS1.1, R_AF2.1, R_AF_BIAS1.1, R_AF_BIAS2.2, U1.5 (SENSOR_VN)
/AIRFRAME_AUDIO_AC: C_AF1.2, R_AF2.2
/AIRFRAME_AUDIO_IN: J5.1, J5.2, R_AF1.2
/AIRFRAME_R1_OUT: C_AF1.1, R_AF1.1
/AMP_OUT_FILTERED: C_AC_COUPLE1.1, C_HP_FILTER1.1, L3.2
/AMP_OUT_P: L3.1, U15.9 (OUTP)
/ATC_AUDIO: C8.2, R18.2, R19.1
/ATC_BTN: CN3.1, R40.2, U1.9 (IO33)
/AUDIO_L_IN: C8.1, CABLE2.1
/AUDIO_OUT_L: C_OUT_L1.2, J2.1, J4.1
/AUDIO_OUT_N: U15.10 (OUTN)
/AUDIO_OUT_R: C_OUT_R1.2, J2.2, J4.2
/AUDIO_R_IN: CABLE2.2
/BATT_SENSE: C29.1, R8.2, R9.1, U1.6 (IO34)
/BAT_NEG: BT1.2 (-), C14.1, Q1.1 (S1), U12.6 (GND)
/BAT_SW: C6.2, C9.2, Q4.3 (D), U9.4 (EN), U9.5 (IN), U10.4 (EN), U10.5 (IN)
/DISP_BL: FPC1.8, U1.31 (IO19)
/DISP_CS: FPC1.5, U1.29 (IO5)
/DISP_DC: FPC1.6, U1.24 (IO2)
/DISP_MISO: FPC1.9
/DISP_MOSI: FPC1.3, U1.37 (IO23)
/DISP_RST: FPC1.7, R_BTN_BASE2.1
/DISP_SCK: FPC1.4, U1.30 (IO18)
/EN: C17.2, Q3.3 (C), R27.2, U1.3 (EN)
/ENC_A: FPC1.15, U1.16 (IO13)
/ENC_B: FPC1.16, U1.13 (IO14)
/ENC_SW: FPC1.17, U1.26 (IO4)
/ESP_I2S_BCLK: U1.12 (IO27), U15.16 (BCLK)
/ESP_I2S_DOUT: U1.10 (IO25), U15.1 (DIN)
/ESP_I2S_WS: U1.11 (IO26), U15.14 (LRCLK)
/ESP_RXD: U1.34 (RXD0), U14.2 (TXD)
/ESP_TXD: U1.35 (TXD0), U14.3 (RXD)
/FB_5V: R16.2, R17.1, U10.3 (FB)
/FB_12V: R14.2, R15.1, U9.3 (FB)
/HP_AUDIO_IN: C_AC_COUPLE1.2, U16.2 (IN1-), U16.6 (IN2-)
/IO0: Q2.3 (C), R28.2, U1.28 (NC)
/J3_DETECT: J3.2, U1.23 (IO15)
/LED_A: R6.2
/LED_NET: R6.1
/MIC_ADC: C23.1, R2.2, R32.2, R34.2, R35.1, U1.4 (SENSOR_VP)
/MIC_HOT_RAW: CABLE1.1, R1.1, R29.1, R33.2
/MIC_PROTECTED: C22.1, J3.1, J4.3, R2.1, R32.1
/MIC_R1_OUT: C22.2, R1.2, R29.2
/PTT_BTN: CN2.1, R41.2, U1.7 (IO35)
/PWR_BTN_SIG: FPC1.18, R_BTN_BASE1.1, U1.14 (IO12)
/PWR_HOLD: R_HOLD_BASE1.1, U1.8 (IO32)
/RTC_INT: U2.3 (~INT/SQW)
/SD_CS: FPC1.14
/SW_5V: L2.1, U10.1 (SW)
/SW_12V: L1.1, U9.1 (SW)
/TOUCH_INT: FPC1.12
/TOUCH_RST: FPC1.13, R_BTN_BASE3.1
/TOUCH_SCL: FPC1.11, U1.36 (IO22), U2.16 (SCL), U3.4 (SCK)
/TOUCH_SDA: FPC1.10, U1.33 (IO21), U2.15 (SDA), U3.3 (SDI)
/UART_DTR: Q2.2 (E), R30.2, U14.13 (~DTR)
/UART_RTS: Q3.2 (E), R31.2, U14.14 (~RTS)
/USB_CC1: J1.A5 (CC1), R25.1
/USB_CC2: J1.B5 (CC2), R26.1
/USB_DN: J1.A7 (D-), J1.B7 (D-), U14.6 (UD-)
/USB_DP: J1.A6 (D+), J1.B6 (D+), U14.5 (UD+)
/USB_VBUS: C12.2, J1.A4 (VBUS), J1.A9 (VBUS), J1.B4 (VBUS), J1.B9 (VBUS), R22.1, R23.1, U11.4 (VCC), U11.8 (CE)
/VBAT: BT2.1, C2.2, U2.14 (VBAT)
unnamed: D1.1 (K), L1.2
unnamed: D3.1 (K), L2.2
unnamed: D4.2 (A), R22.2
unnamed: D4.1 (K), U11.7 (~CHRG)
unnamed: D5.2 (A), R23.2
unnamed: D5.1 (K), U11.6 (~STDBY)
unnamed: Q1.6 (G1), U12.3 (OC)
unnamed: Q1.4 (G2), U12.1 (OD)
unnamed: Q2.1 (B), R31.1
unnamed: Q3.1 (B), R30.1
unnamed: Q4.1 (G), Q5.3 (C), R_PWR_PU1.1
unnamed: Q5.1 (B), R_BASE_PD1.2, R_BTN_BASE1.2, R_HOLD_BASE1.2
unnamed: R28.1, U1.25 (IO0)
unnamed: C13.1, U11.5 (BAT)
unnamed: R20.1, U11.2 (PROG)
unnamed: R21.1, U11.1 (TEMP)
unnamed: C14.2, R24.2, U12.5 (VCC)
unnamed: C21.2, U14.4 (V3)
unnamed: C20.2, U14.16 (VCC)
unnamed: R36.2, U15.4 (~SD_MODE)
unnamed: C_BYPASS1.2, U16.3 (BYPASS)
unnamed: R_SHUTDOWN1.2, U16.5 (SHUTDOWN)
unnamed: C_OUT_L1.1, U16.1 (VO1)
unnamed: C_OUT_R1.1, U16.7 (VO2)

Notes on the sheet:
INSERT CELL FLAT END HERE
HEADPHONE AMP

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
